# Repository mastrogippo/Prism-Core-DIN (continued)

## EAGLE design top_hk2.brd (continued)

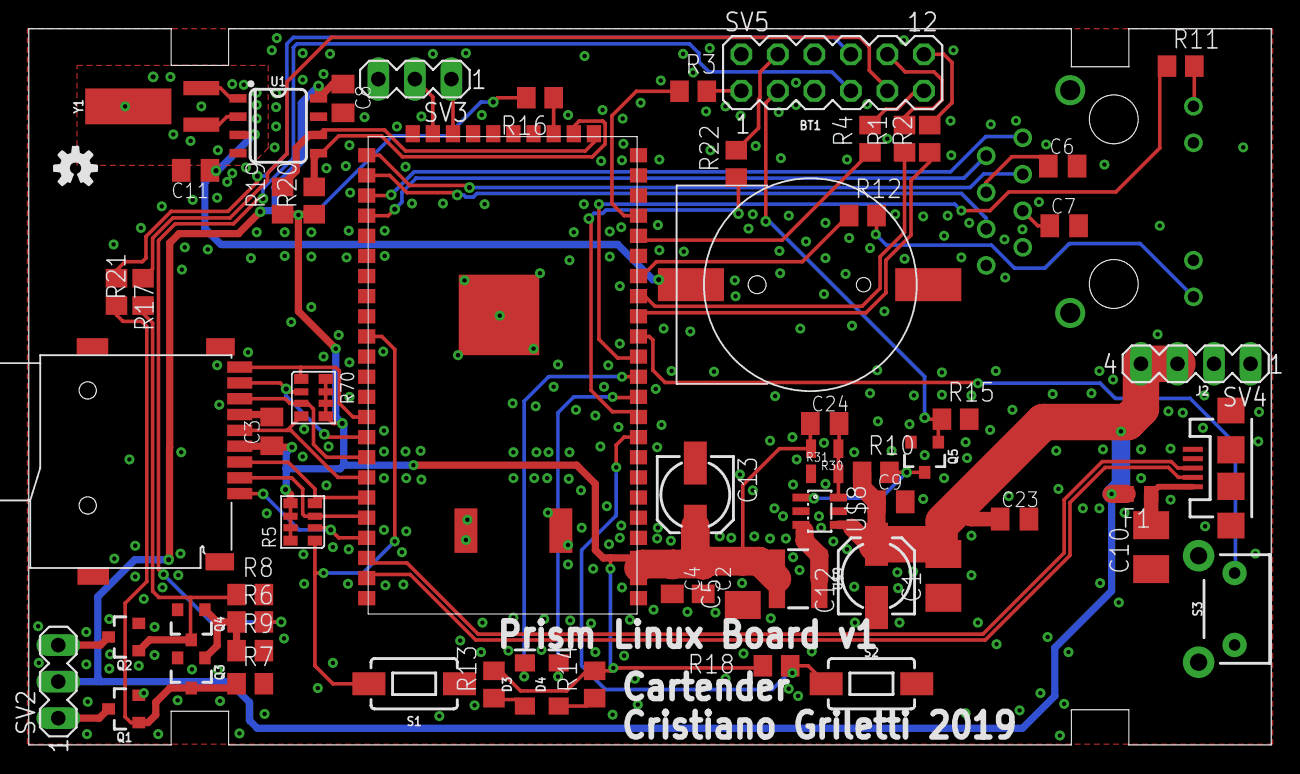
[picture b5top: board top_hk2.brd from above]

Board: 2 copper layers, 86.4 x 49.8 mm, 65 parts (1 on the bottom side), 60 nets.
